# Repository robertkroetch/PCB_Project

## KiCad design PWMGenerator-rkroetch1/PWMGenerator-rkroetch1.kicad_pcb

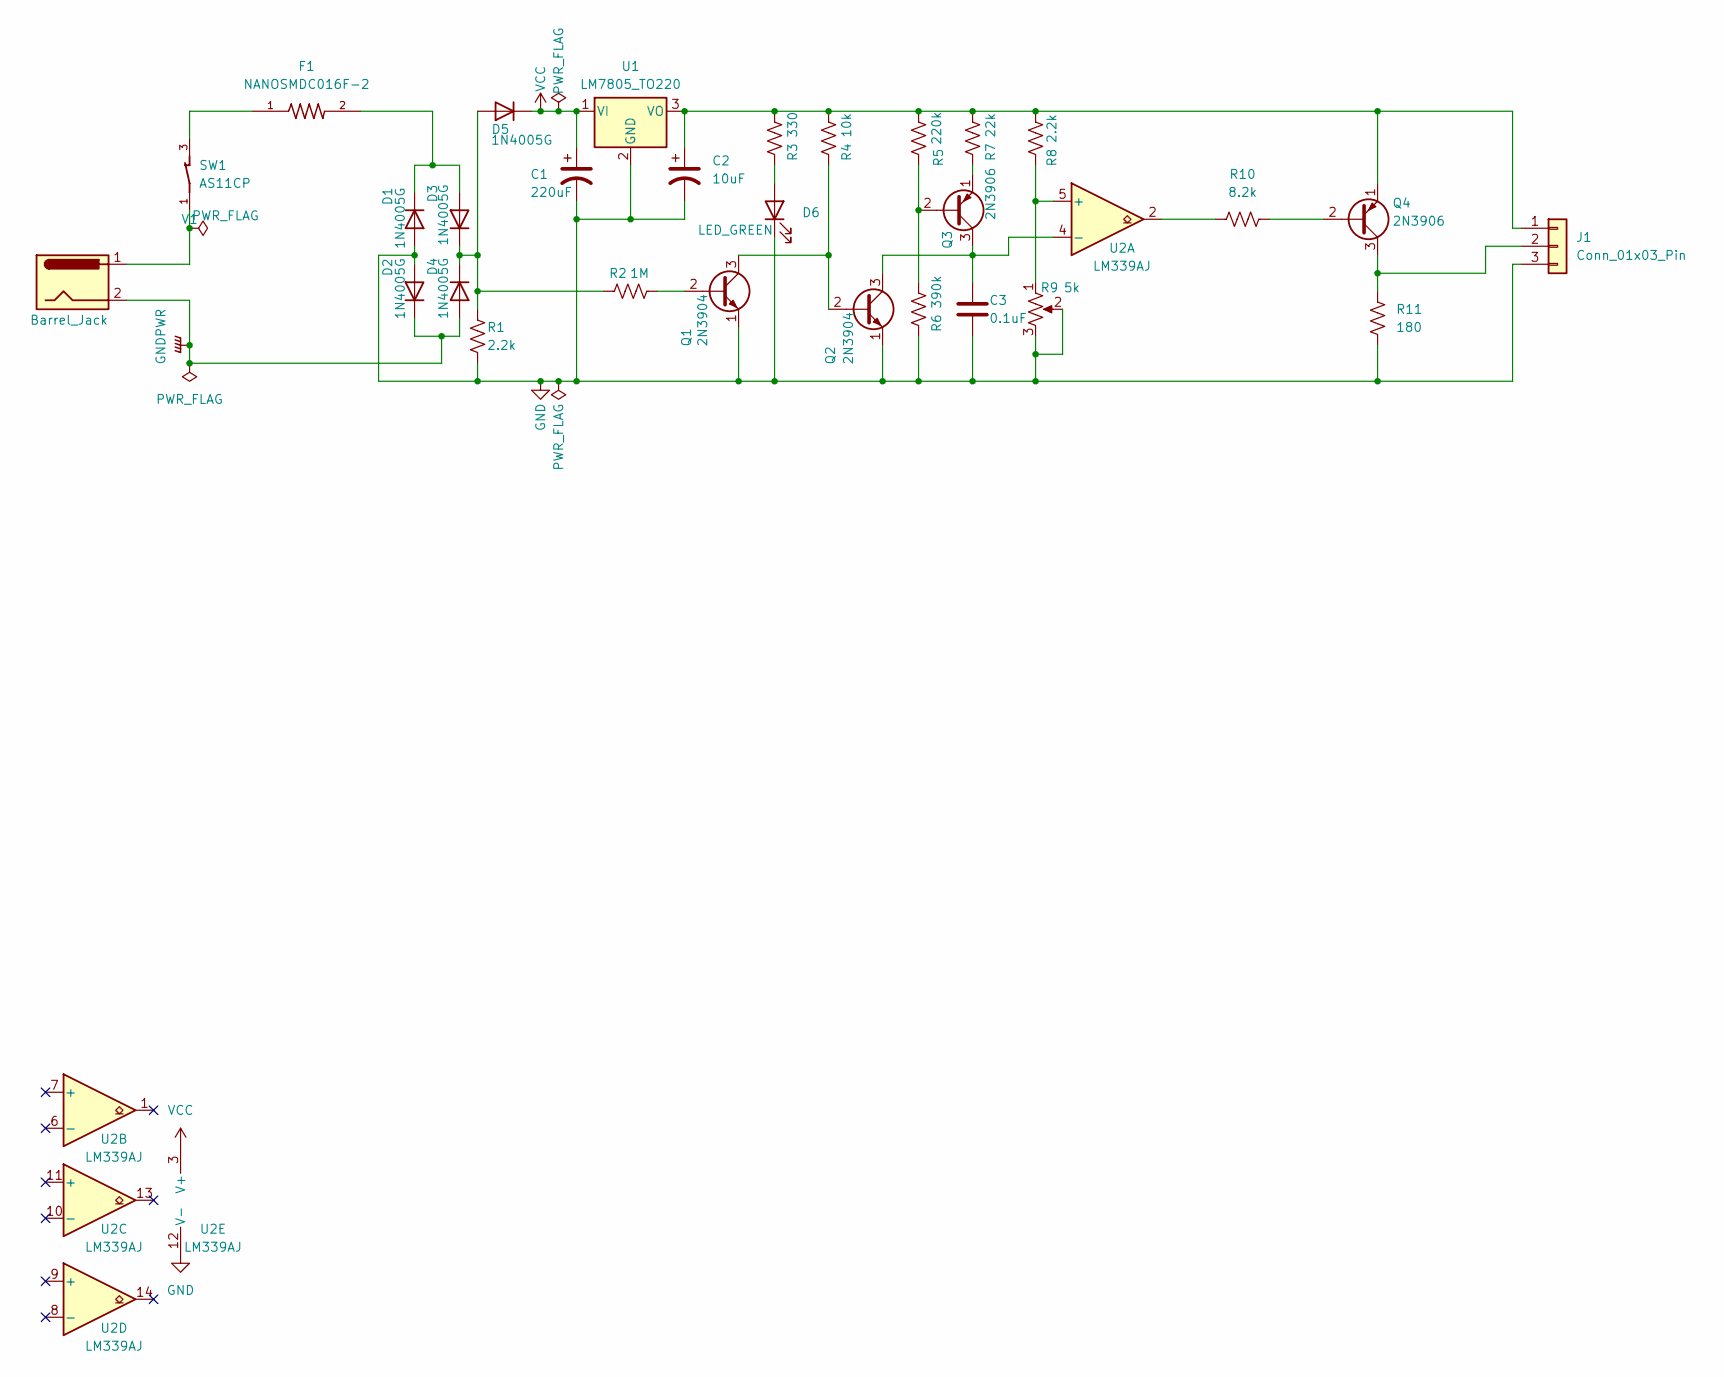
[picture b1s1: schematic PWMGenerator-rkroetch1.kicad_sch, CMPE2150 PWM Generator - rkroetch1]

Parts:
C1: 220uF; CP_Radial_D8.0mm_P3.50mm
C2: 10uF; CP_Radial_D10.0mm_P5.00mm
C3: 0.1uF; C_0805_2012Metric
D1, D2, D3, D4, D5: 1N4005G; D_DO-41_SOD81_P10.16mm_Horizontal
D6: LED_GREEN; LED_D5.0mm
F1: NANOSMDC016F-2; RESC3115X65N
J1: Conn_01x03_Pin; PinHeader_1x03_P2.54mm_Vertical
Q1, Q2: 2N3904; TO-92_Inline
Q3, Q4: 2N3906; TO-92_Inline
R1, R8: 2.2k; R_0805_2012Metric
R2: 1M; R_0805_2012Metric
R3: 330; R_0805_2012Metric
R4: 10k; R_0805_2012Metric
R5: 220k; R_0805_2012Metric
R6: 390k; R_0805_2012Metric
R7: 22k; R_0805_2012Metric
R9: 5k; Potentiometer_Piher_PT-15-V15_Vertical_Hole
R10: 8.2k; R_0805_2012Metric
R11: 180; R_0805_2012Metric
SW1: AS11CP; SW_AS11CP; PARTREV N/A
U1: LM7805_TO220; TO-220-3_Vertical
U2: LM339AJ; SOIC-14_3.9x8.7mm_P1.27mm
V1: Barrel_Jack; BarrelJack_SwitchcraftConxall_RAPC10U_Horizontal

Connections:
GND: C1.2, C2.2, C3.2, D1.2 (A), D2.2 (A), D6.1 (K), J1.3, Q1.1 (E), Q2.1 (E), R1.2, R6.2, R9.2, R9.3, R11.2, U1.2 (GND), U2.12 (V-)
GNDPWR: D2.1 (K), D4.2 (A), V1.2
unnamed: D1.1 (K), D3.2 (A), F1.2
unnamed: D3.1 (K), D4.1 (K), D5.2 (A), R1.1, R2.1
unnamed: D6.2 (A), R3.2
unnamed: F1.1, SW1.3
unnamed: C2.1, J1.1, Q4.1 (E), R3.1, R4.1, R5.1, R7.1, R8.1, U1.3 (VO)
unnamed: J1.2, Q4.3 (C), R11.1
unnamed: Q1.2 (B), R2.2
unnamed: Q1.3 (C), Q2.2 (B), R4.2
unnamed: C3.1, Q2.3 (C), Q3.3 (C), U2.4 (-)
unnamed: Q3.2 (B), R5.2, R6.1
unnamed: Q3.1 (E), R7.2
unnamed: Q4.2 (B), R10.2
unnamed: R10.1, U2.2
unnamed: SW1.1, V1.1
unnamed: R8.2, R9.1, U2.5 (+)
VCC: C1.1, D5.1 (K), U1.1 (VI), U2.3 (V+)

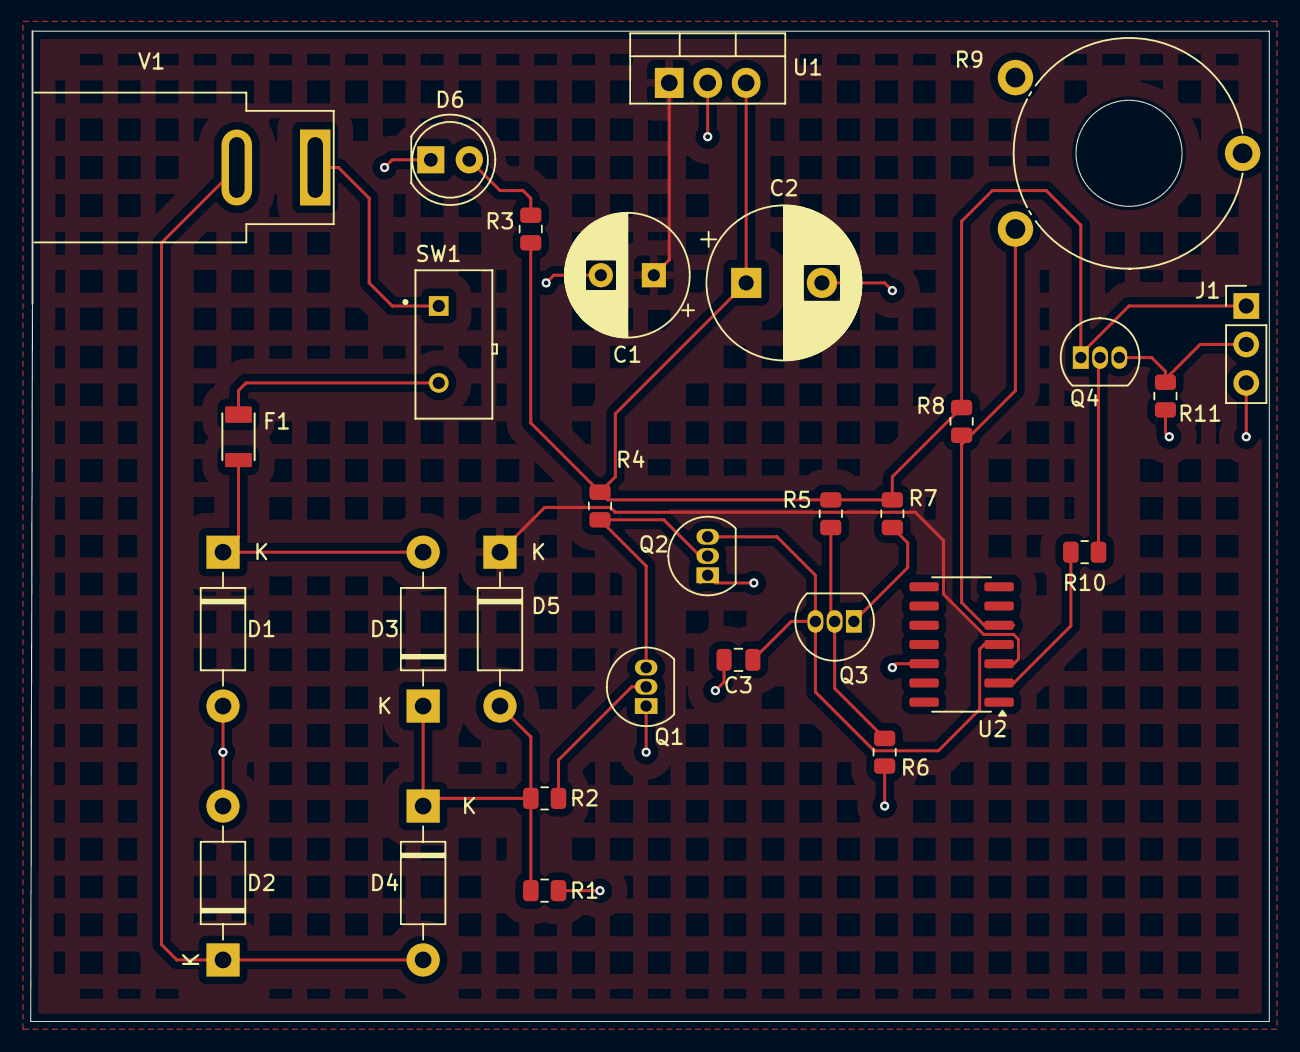
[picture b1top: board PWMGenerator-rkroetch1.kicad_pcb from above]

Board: 2 copper layers, 81.8 x 65.4 mm, 30 parts (0 on the bottom side), 18 nets.

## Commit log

2025-12-12 Readme
2025-12-12 KiCad init
2025-12-13 PCB Part A done, I think
2025-12-16 PCB Part B Part 2
2025-12-16 PCB Part B Part 3
2025-12-16 Part C Init
2025-12-16 Update Jack footprint, finish part 2
2025-12-16 Fill zones
2025-12-16 No errors/warnings
2025-12-16 Aligned text a little better
2025-12-17 Whatever
